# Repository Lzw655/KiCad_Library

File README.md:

# KiCad Libraries & Projects

## Plugins

### Manufacturing BOM and Gerbers

* [kicad-jlcpcb-tools](https://github.com/Bouni/kicad-jlcpcb-tools): JLCPCB Tools

### View

* Interactive Html Bom (internal): Generate Interactive HTML BOM
* Board2Pdf (internal): Board2Pdf

### Tools

* KiBuzzard (internal): Create Labels
* [pcb-action-tools (modified)](./3rdparty/custom/plugins/pcb-action-tools_v1.0.6~_pcm.zip):
    * Annular checker
    * Snap Selected Footprint(s) to Grid
    * Move Selected Drawings to chosen Layer
* KiKit & KiKit Library (internal) ([Installation Guide](https://yaqwsx.github.io/KiKit/v1.4/installation/intro/)):
    * KiKit: Show/hide references
    * KiKit: Panelize PCB

## Libraries

### SoC

* [Espressif kicad-libraries](https://github.com/espressif/kicad-libraries)

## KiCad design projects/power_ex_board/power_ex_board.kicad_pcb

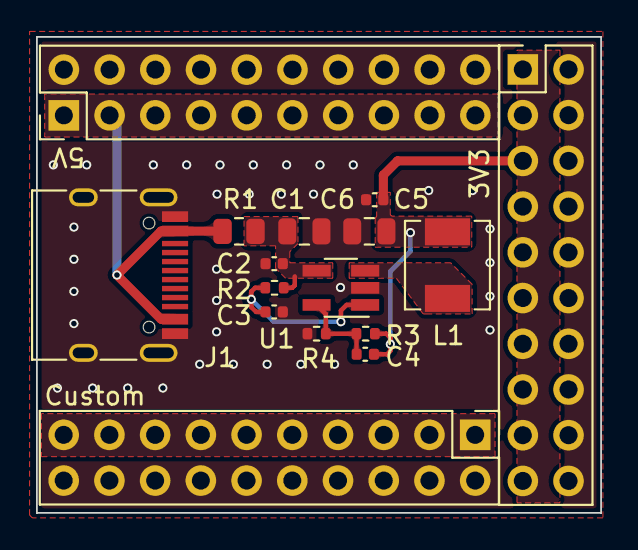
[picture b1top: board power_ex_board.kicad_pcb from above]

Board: 2 copper layers, 31.3 x 26.4 mm, 16 parts (0 on the bottom side), 8 nets.

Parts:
3V3: 3V3; PinHeader_2x10_P2.54mm_Vertical
5V: 5V; PinHeader_2x10_P2.54mm_Vertical
C1, C6: 10uF/16V(10%); C_0805_2012Metric
C2: 100nF/16V(10%); C_0402_1005Metric
C3: 1uF/16V(10%)(NC); C_0402_1005Metric
C4: 22pF/50V(5%); C_0402_1005Metric
C5: 100nF/10V(5%); C_0402_1005Metric
Custom: Custom; PinHeader_2x10_P2.54mm_Vertical
J1: USB_C_Receptacle_USB2.0; USB_C_Receptacle_HRO_TYPE-C-31-M-12
L1: 2.2uH(20%); L_Sunlord_MWSA0402S
R1: 0(1%); R_0805_2012Metric
R2: 10K(1%); R_0402_1005Metric
R3: 680K(1%); R_0402_1005Metric
R4: 150K(1%); R_0402_1005Metric
U1: ETA3409S2F; SOT-23-5_HandSoldering

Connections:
+3V3: 3V3.1, 3V3.3, 3V3.5, 3V3.7, 3V3.9, 3V3.11, 3V3.13, 3V3.15, 3V3.17, 3V3.19, C4.1, C5.1, C6.1, L1.2, R3.1
+5V: 5V.1, 5V.3, 5V.5, 5V.7, 5V.9, 5V.11, 5V.13, 5V.15, 5V.17, 5V.19, J1.A4 (VBUS), J1.A9 (VBUS), J1.B4 (VBUS), J1.B9 (VBUS), R1.1
GND: 3V3.2, 3V3.4, 3V3.6, 3V3.8, 3V3.10, 3V3.12, 3V3.14, 3V3.16, 3V3.18, 3V3.20, 5V.2, 5V.4, 5V.6, 5V.8, 5V.10, 5V.12, 5V.14, 5V.16, 5V.18, 5V.20, C1.2, C2.2, C3.2, C5.2, C6.2, Custom.2, Custom.4, Custom.6, Custom.8, Custom.10, Custom.12, Custom.14, Custom.16, Custom.18, Custom.20, J1.A1 (GND), J1.A12 (GND), J1.B1 (GND), J1.B12 (GND), J1.S1 (SHIELD), R4.2, U1.2 (GND)
unnamed: C3.1, R2.1, U1.1 (EN)
unnamed: C4.2, R3.2, R4.1, U1.5 (FB)
unnamed: C1.1, C2.1, R1.2, R2.2, U1.4 (IN)
unnamed: L1.1, U1.3 (LX)
VCC: Custom.1, Custom.3, Custom.5, Custom.7, Custom.9, Custom.11, Custom.13, Custom.15, Custom.17, Custom.19

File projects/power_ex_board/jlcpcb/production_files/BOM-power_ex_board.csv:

Comment,Designator,Footprint,LCSC
100nF/16V(10%),"C2,C5",C_0402_1005Metric,C1525
22pF/50V(5%),C4,C_0402_1005Metric,C1555
10uF/16V(10%),"C1,C6",C_0805_2012Metric,C15850
0(1%),R1,R_0805_2012Metric,C17477
10K(1%),R2,R_0402_1005Metric,C25744
150K(1%),R4,R_0402_1005Metric,C25755

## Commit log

2023-09-21 init
2023-09-21 projects: add power_ex_board
